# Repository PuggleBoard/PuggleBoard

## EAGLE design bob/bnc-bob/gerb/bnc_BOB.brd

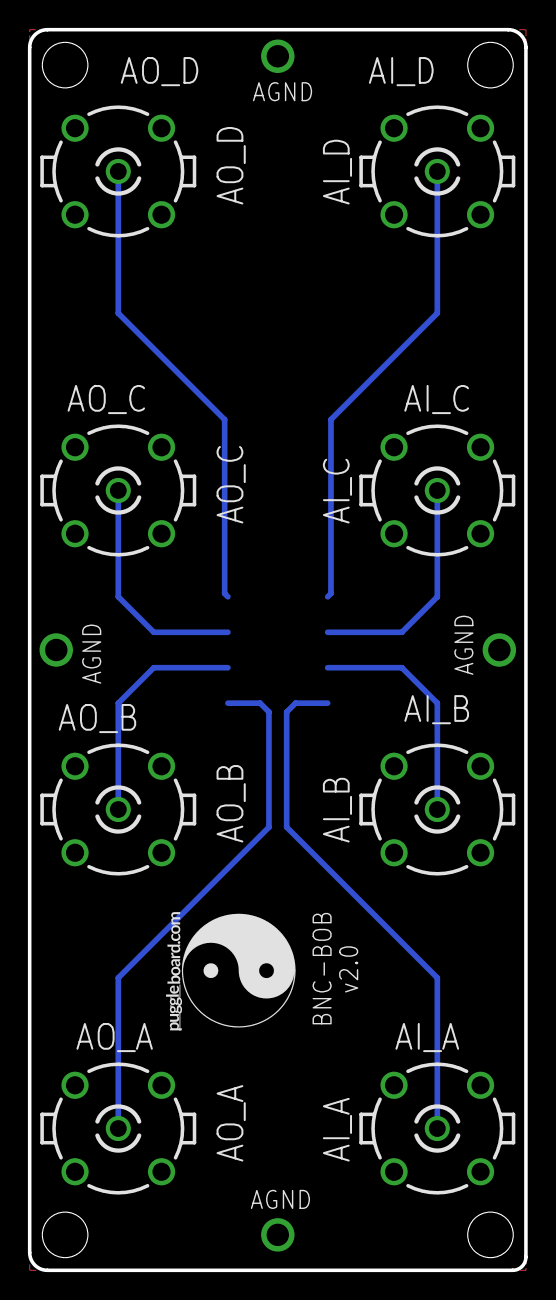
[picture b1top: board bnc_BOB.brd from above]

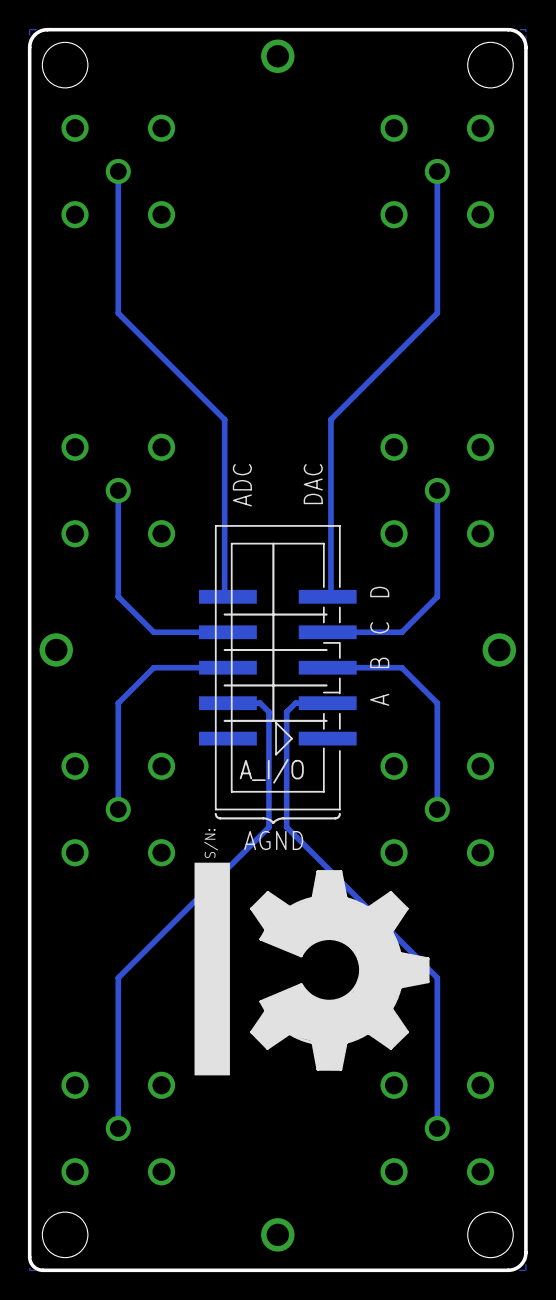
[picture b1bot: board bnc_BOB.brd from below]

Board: 2 copper layers, 35.6 x 88.9 mm, 11 parts (2 on the bottom side), 9 nets.

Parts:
AI_A: 5-1634503-1; B35N61
AI_B: 5-1634503-1; B35N61
AI_C: 5-1634503-1; B35N61
AI_D: 5-1634503-1; B35N61
AO_A: 5-1634503-1; B35N61
AO_B: 5-1634503-1; B35N61
AO_C: 5-1634503-1; B35N61
AO_D: 5-1634503-1; B35N61
A_I/O: PINHD-2X5-IDC-SMD; 2X05-IDC-SMD
U$1: PB-LOGO
U$2: OSHW_FILLX500_NOTEXT

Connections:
ADC_A: AI_A.1, A_I/O.P$4
ADC_B: AI_B.1, A_I/O.P$6
ADC_C: AI_C.1, A_I/O.P$8
ADC_D: AI_D.1, A_I/O.P$10
AGND: AI_A.2, AI_A.3, AI_A.4, AI_A.5, AI_B.2, AI_B.3, AI_B.4, AI_B.5, AI_C.2, AI_C.3, AI_C.4, AI_C.5, AI_D.2, AI_D.3, AI_D.4, AI_D.5, AO_A.2, AO_A.3, AO_A.4, AO_A.5, AO_B.2, AO_B.3, AO_B.4, AO_B.5, AO_C.2, AO_C.3, AO_C.4, AO_C.5, AO_D.2, AO_D.3, AO_D.4, AO_D.5, A_I/O.P$1, A_I/O.P$2
DAC_A: AO_A.1, A_I/O.P$3
DAC_B: AO_B.1, A_I/O.P$5
DAC_C: AO_C.1, A_I/O.P$7
DAC_D: AO_D.1, A_I/O.P$9

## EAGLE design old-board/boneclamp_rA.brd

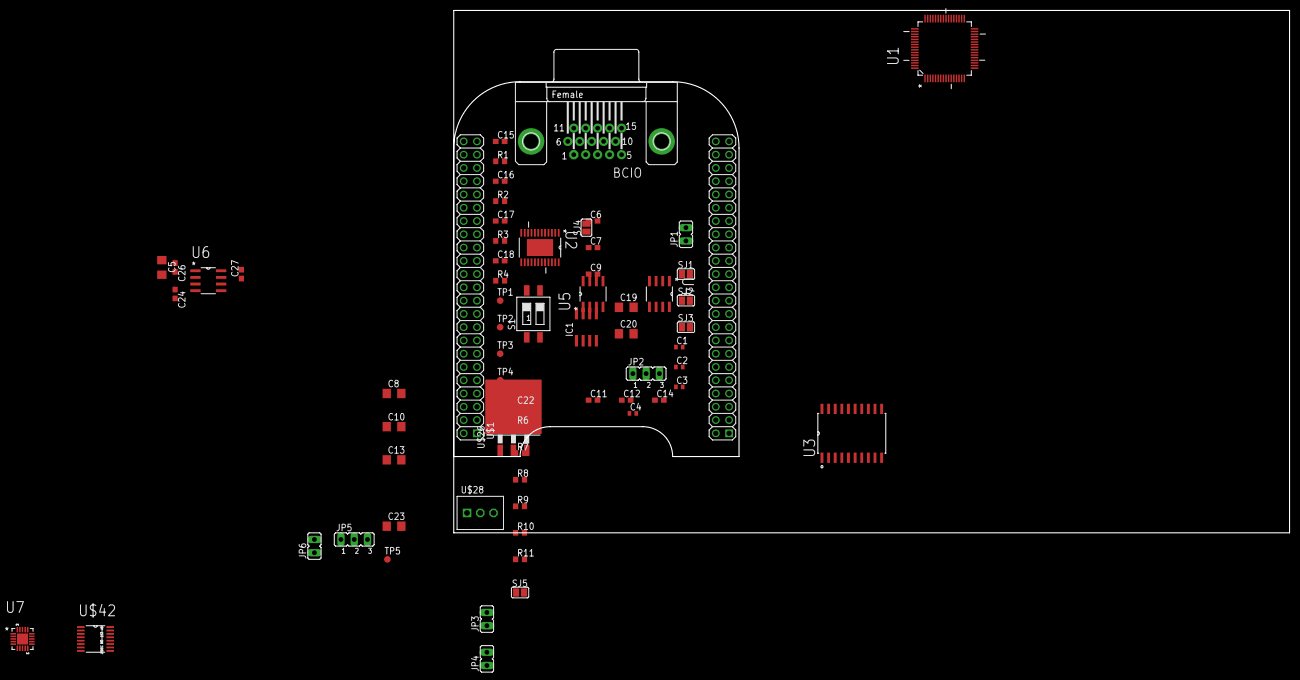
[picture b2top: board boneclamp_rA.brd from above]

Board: 4 copper layers, 160.0 x 100.0 mm, 65 parts (0 on the bottom side), 43 nets, no tracks yet.

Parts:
BCIO: F15-SHEILD; HDF15H
C1, C2, C3, C4: 1 uF; C0402
C5, C8, C10, C13, C19, C20, C23: 10uF; C1206
C6, C7, C9, C11, C12, C14, C22, C24, C26, C27: 0.1uF; C0603
C15, C16, C17, C18: C0603
IC1: 24C; SO-08
JP1, JP3, JP4, JP6: JP1
JP2, JP5: JP2
R1, R2, R3, R4: R0603
R6, R10: 5.6k; R0603
R7, R8, R9: 4.75k; R0603
R11: 10k; R0603
S1: SWS002; SMS-002
SJ1, SJ2, SJ3, SJ4, SJ5: SJ
TP1, TP2, TP3, TP4, TP5: TPB1,27; B1,27
U1: AD7656YSTZ; QFP50P1200X1200X160-64N
U2: AD5754RBREZ; SOP65P640X120-25N
U3: SN74ABT541BDW; SOIC127P1030X265-20N
U4, U5: ADP3303ARZ-5; SOIC127P600X175-8N
U6: ADR431BRZ; SOIC127P600X175-8N
U7: AD7682BCPZ; QFN50P400X400X100-21N
U$1: BEAGLEBONE_OUTLINE; BEAGLEBONE_SHIELD
U$26: LM1085; TO263-3
U$28: SCREW3
U$42: AD5686RARUZ; MO-153-AB

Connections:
+12V: C19.1, U$26.3
AGND: BCIO.1, C1.2, C2.2, C3.2, C4.2, C5.2, C6.2, C9.2, C10.2, C16.2, C17.2, C18.2, C23.2, C24.2, C26.2, JP1.2, R2.1, R3.1, R4.1, SJ4.1, U1.32, U1.37, U1.38, U1.43, U1.44, U1.49, U1.52, U1.53, U1.57, U1.59, U4.4, U5.4, U6.4, U$1.1, U$1.2, U$1.47, U$1.48, U$1.89, U$1.90, U$1.91
AVCC: C7.1, C9.1, C10.1, U4.1, U4.2
BB_5V: C5.1, C6.1, C8.1, C11.1, U4.5, U4.7, U4.8, U5.5, U5.7, U5.8, U$1.53, U$1.54
CONVST: U1.21, U1.22, U1.23
DAC_A: BCIO.8, C18.1, R4.2, TP1.TP, U2.3
DAC_B: BCIO.9, C17.1, R3.2, TP2.TP, U2.4
DAC_C: BCIO.10, C16.1, R2.2, TP3.TP, U2.23
DAC_D: BCIO.11, C15.1, R1.2, TP4.TP, U2.22
DGND: C8.2, C11.2, C13.2, C14.2, C19.2, C20.2, C22.2, IC1.4, JP2.3, S1.3, S1.4, SJ4.2, U1.8, U1.25, U$1.92, U$26.1
DVCC: C12.1, C13.1, C14.1, U1.26, U2.14, U5.1, U5.2
I2C2_SCL: IC1.6, R10.1, U$1.65
I2C2_SDA: IC1.5, R6.1, U$1.66
unnamed: BCIO.2, U1.33
unnamed: BCIO.3, U1.36
unnamed: BCIO.4, U1.39
unnamed: BCIO.5, U1.42
unnamed: BCIO.6, U1.45
unnamed: BCIO.7, U1.48
unnamed: SJ1.1, U2.16
unnamed: SJ2.2, SJ3.2, U2.9
unnamed: C2.1, U1.56
unnamed: C1.1, U1.58
unnamed: JP2.2, U1.27
unnamed: C4.1, U1.34, U1.35, U1.40, U1.41, U1.46, U1.47, U1.50, U1.60
unnamed: IC1.1, R7.1, R8.1, S1.1
unnamed: C12.2, U5.3
unnamed: C7.2, U4.3
unnamed: C15.2, R1.1
unnamed: IC1.2, S1.2
unnamed: IC1.3, R9.1
unnamed: JP3.1, U1.51
unnamed: IC1.7, SJ5.1
unnamed: R11.1, SJ5.2
unnamed: JP4.1, U2.17
unnamed: C26.1, U6.1
SGND: BCIO.P$1, BCIO.P$2, JP1.1
VDD: C23.1, C24.1, U1.31, U2.24, U6.2, U7.20, U$42.5
VDD_BB: C20.1, U$1.51, U$1.52, U$26.2, U$26.TAB
VDRIVE: C22.1, IC1.8, JP2.1, R6.2, R7.2, R8.2, R9.2, R10.2, R11.2, U$1.49, U$1.50
VREF_2.5V: JP3.2, JP4.2, JP5.2
VREF_OUT: C27.1, JP5.3, JP6.2, TP5.TP, U6.6
VSS: U1.30, U2.1

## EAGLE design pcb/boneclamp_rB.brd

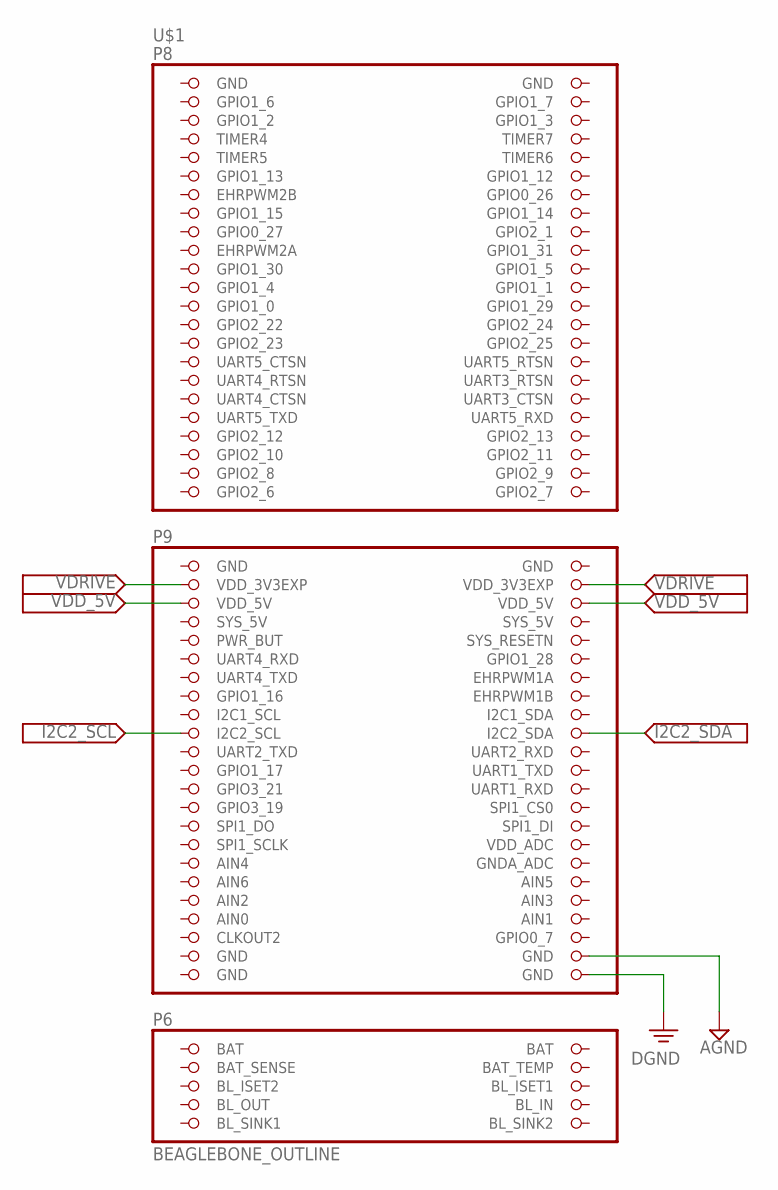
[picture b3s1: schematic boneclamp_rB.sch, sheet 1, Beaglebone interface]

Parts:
U$1: BEAGLEBONE_OUTLINE; BEAGLEBONE_SHIELD

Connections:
AGND: U$1.90 (GND); also elsewhere on the board
AIN0: U$1.85 (AIN0)
BAT_SENSE: U$1.95 (BAT_SENSE)
BL_IN: U$1.97 (BL_IN)
BL_OUT: U$1.100 (BL_OUT)
BL_SINK1: U$1.101 (BL_SINK1)
BL_SINK2: U$1.102 (BL_SINK2)
DGND: U$1.92 (GND); also elsewhere on the board
GND: U$1.1 (GND), U$1.2 (GND), U$1.47 (GND), U$1.48 (GND), U$1.89 (GND), U$1.91 (GND); also elsewhere on the board
I2C2_SCL: U$1.65 (I2C2_SCL); also elsewhere on the board
I2C2_SDA: U$1.66 (I2C2_SDA); also elsewhere on the board
SYS_5V: U$1.53 (SYS_5V)
VDD_5V: U$1.51 (VDD_5V), U$1.52 (VDD_5V); also elsewhere on the board
VDRIVE: U$1.49 (VDD_3V3EXP), U$1.50 (VDD_3V3EXP); also elsewhere on the board

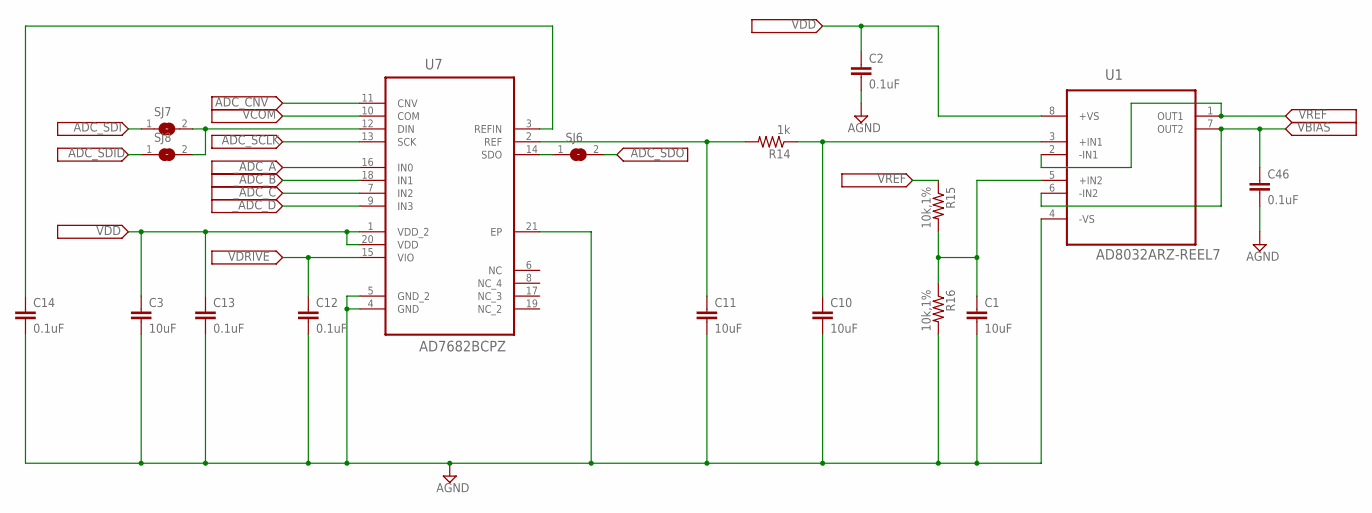
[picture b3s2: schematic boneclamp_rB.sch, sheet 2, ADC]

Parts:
C1, C3, C10, C11: 10uF; C0805
C2, C12, C13, C14, C46: 0.1uF; C0805
R14: 1k; R0805
R15, R16: 10k,1%; R0805
SJ6, SJ7, SJ8: SJ
U1: AD8032ARZ-REEL7; SOIC127P600X175-8N
U7: AD7682BCPZ; QFN50P400X400X100-21N

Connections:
ADC_CNV: U7.11 (CNV)
ADC_SCLK: U7.13 (SCK)
ADC_SDI: SJ7.1
ADC_SDID: SJ8.1
ADC_SDO: SJ6.2
AGND: C1.2, C2.2, C3.2, C10.2, C11.2, C12.2, C13.2, C14.2, C46.2, R16.2, U1.4 (-VS), U7.4 (GND), U7.5 (GND_2), U7.21 (EP); also elsewhere on the board
unnamed: C1.1, R15.2, R16.1, U1.5 (+IN2)
unnamed: SJ7.2, SJ8.2, U7.12 (DIN)
unnamed: C11.1, R14.2, U7.2 (REF)
unnamed: C10.1, R14.1, U1.3 (+IN1)
unnamed: C14.1, U7.3 (REFIN)
VBIAS: C46.1, U1.6 (-IN2), U1.7 (OUT2); also elsewhere on the board
VCOM: U7.10 (COM)
VDD: C2.1, C3.1, C13.1, U1.8 (+VS), U7.1 (VDD_2), U7.20 (VDD); also elsewhere on the board
VDRIVE: C12.1, U7.15 (VIO); also elsewhere on the board
VREF: R15.1, U1.1 (OUT1), U1.2 (-IN1); also elsewhere on the board
_ADC_A: U7.16 (IN0); also elsewhere on the board
_ADC_B: U7.18 (IN1); also elsewhere on the board
_ADC_C: U7.7 (IN2); also elsewhere on the board
_ADC_D: U7.9 (IN3); also elsewhere on the board

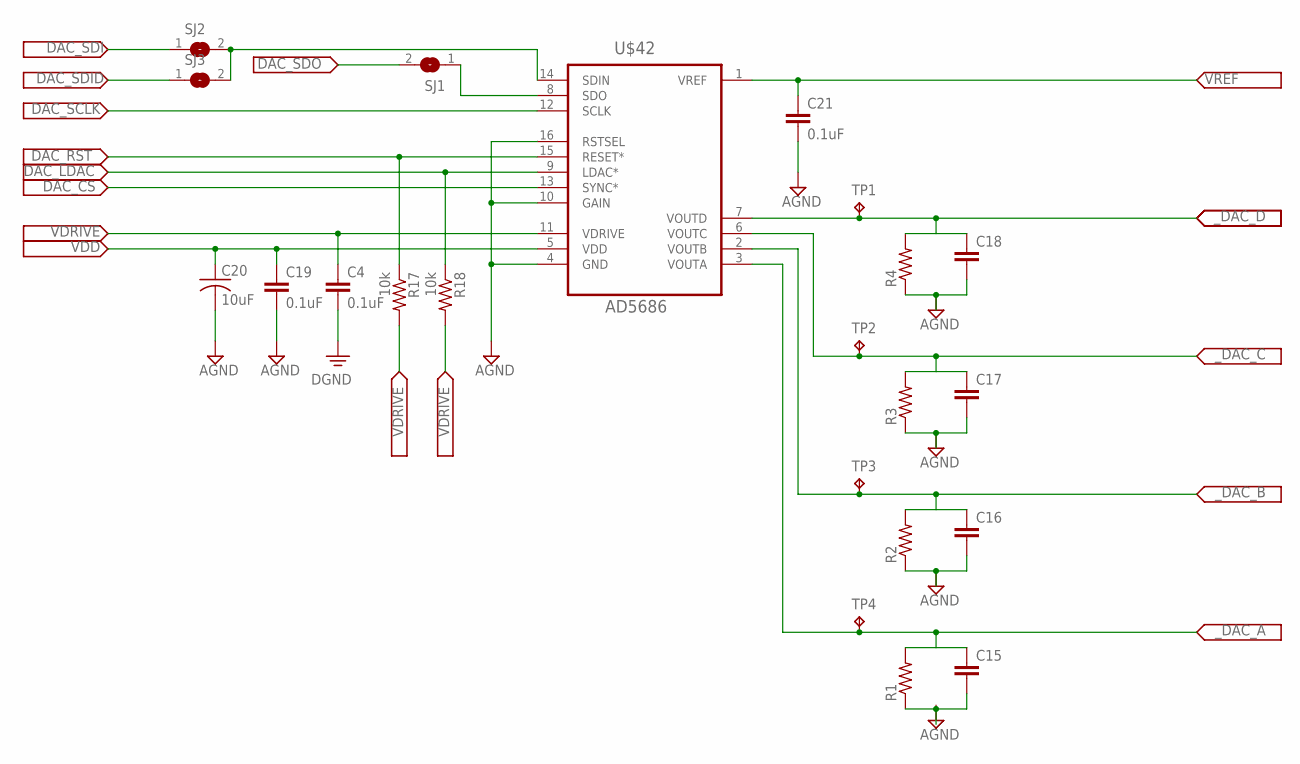
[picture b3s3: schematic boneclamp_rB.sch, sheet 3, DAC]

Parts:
C4, C19, C21: 0.1uF; C0805
C15, C16, C17, C18: C-EUC0805; C0805
C20: 10uF; C0805
R1, R2, R3, R4: R-US_R0805; R0805
R17, R18: 10k; R0805
SJ1, SJ2, SJ3: SJ
TP1, TP2, TP3, TP4: TPB1,27; B1,27
U$42: AD5686; MO-153-AB

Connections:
AGND: C16.2, C17.2, C18.2, C19.2, C20.2, C21.2, R2.1, R3.1, R4.1, U$42.4 (GND), U$42.10 (GAIN), U$42.16 (RSTSEL); also elsewhere on the board
DAC_CS: U$42.13 (SYNC*)
DAC_LDAC: R18.1, U$42.9 (LDAC*)
DAC_RST: R17.1, U$42.15 (RESET*)
DAC_SCLK: U$42.12 (SCLK)
DAC_SDI: SJ2.1
DAC_SDID: SJ3.1
DAC_SDO: SJ1.2
unnamed: SJ1.1, U$42.8 (SDO)
unnamed: SJ2.2, SJ3.2, U$42.14 (SDIN)
unnamed: C15.2, R1.1
PE: C4.2
VDD: C19.1, C20.1, U$42.5 (VDD); also elsewhere on the board
VDRIVE: C4.1, R17.2, R18.2, U$42.11 (VDRIVE); also elsewhere on the board
VREF: C21.1, U$42.1 (VREF); also elsewhere on the board
_DAC_A: C15.1, R1.2, TP4.TP, U$42.3 (VOUTA); also elsewhere on the board
_DAC_B: C16.1, R2.2, TP3.TP, U$42.2 (VOUTB); also elsewhere on the board
_DAC_C: C17.1, R3.2, TP2.TP, U$42.6 (VOUTC); also elsewhere on the board
_DAC_D: C18.1, R4.2, TP1.TP, U$42.7 (VOUTD); also elsewhere on the board

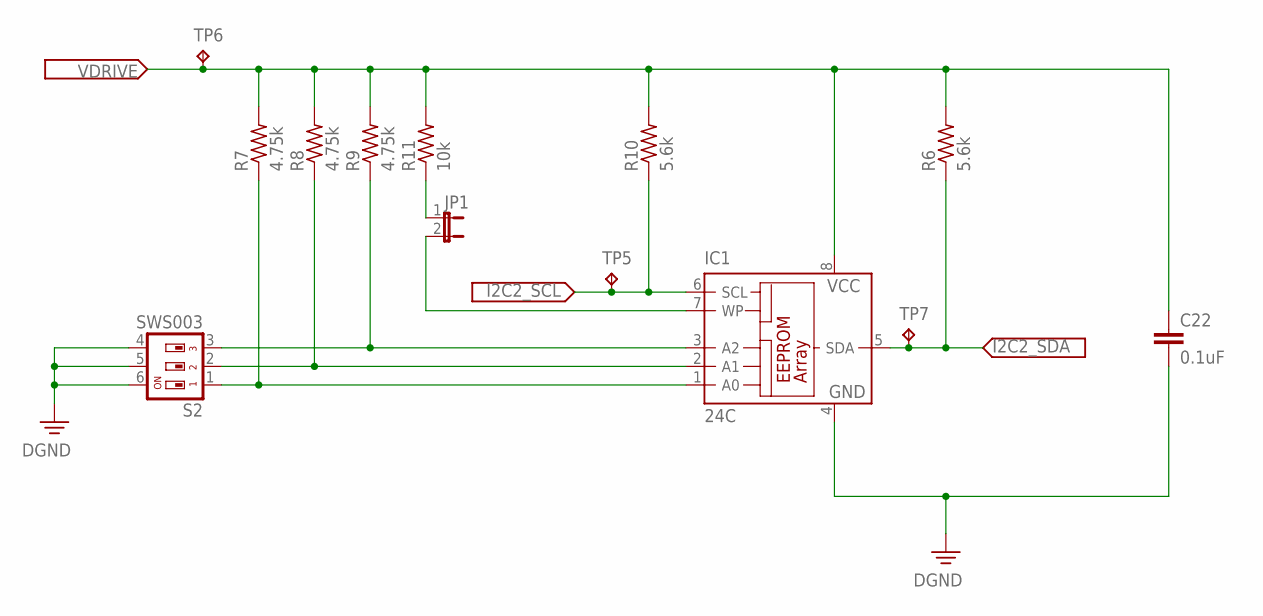
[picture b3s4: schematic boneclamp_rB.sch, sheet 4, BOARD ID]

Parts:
C22: 0.1uF; C0603
IC1: 24C; SO-08
JP1: JP1E; JP1
R6, R10: 5.6k; R0603
R7, R8, R9: 4.75k; R0603
R11: 10k; R0603
S2: SWS003; SMS-003
TP5, TP6, TP7: TPB1,27; B1,27

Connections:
DGND: C22.2, IC1.4 (GND), S2.4, S2.5, S2.6; also elsewhere on the board
I2C2_SCL: IC1.6 (SCL), R10.1, TP5.TP; also elsewhere on the board
I2C2_SDA: IC1.5 (SDA), R6.1, TP7.TP; also elsewhere on the board
unnamed: IC1.1 (A0), R7.1, S2.1
unnamed: IC1.2 (A1), R8.1, S2.2
unnamed: IC1.3 (A2), R9.1, S2.3
unnamed: IC1.7 (WP), JP1.2
unnamed: JP1.1, R11.1
VDRIVE: C22.1, IC1.8 (VCC), R6.2, R7.2, R8.2, R9.2, R10.2, R11.2, TP6.TP; also elsewhere on the board

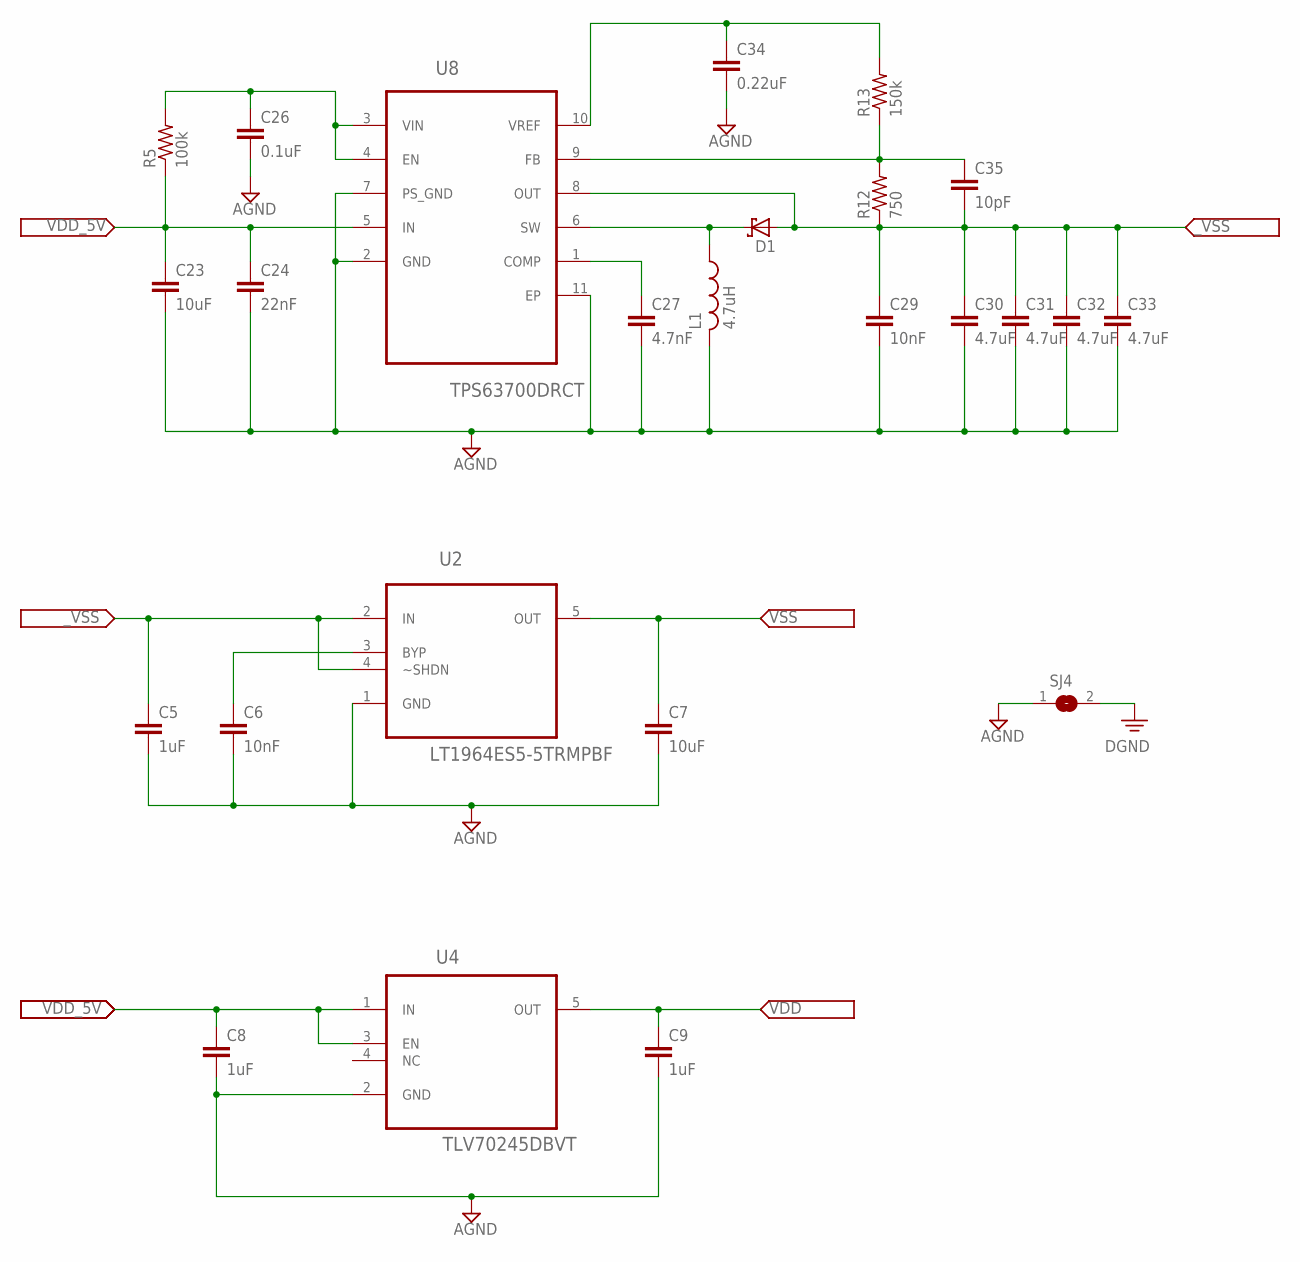
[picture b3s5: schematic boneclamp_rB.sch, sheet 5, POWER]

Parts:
C5, C8, C9: 1uF; C0603
C6, C29: 10nF; C0603
C7, C23: 10uF; C0603
C24: 22nF; C0603
C26: 0.1uF; C0603
C27: 4.7nF; C0603
C30, C31, C32, C33: 4.7uF; C0603
C34: 0.22uF; C0603
C35: 10pF; C0603
D1: SCHOTTKY-DIODE-2; DO-219AB
L1: 4.7uH; L4012M
R5: 100k; R0603
R12: 750; R0603
R13: 150k; R0603
SJ4: SJ
U2: LT1964ES5-5TRMPBF; SOT95P280X100-5N
U4: TLV70245DBVT; SOT95P280X110-5N
U8: TPS63700DRCT; SON50P300X300X100-11N

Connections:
AGND: C5.2, C6.2, C7.2, C8.2, C9.2, C23.2, C24.2, C26.2, C27.2, C29.2, C30.2, C31.2, C32.2, C33.2, C34.2, L1.2, SJ4.1, U2.1 (GND), U4.2 (GND), U8.2 (GND), U8.7 (PS_GND), U8.11 (EP); also elsewhere on the board
DGND: SJ4.2; also elsewhere on the board
unnamed: C6.1, U2.3 (BYP)
unnamed: C26.1, R5.2, U8.3 (VIN), U8.4 (EN)
unnamed: C27.1, U8.1 (COMP)
unnamed: D1.P$1 (A), L1.1, U8.6 (SW)
unnamed: C35.1, R12.2, R13.1, U8.9 (FB)
unnamed: C34.1, R13.2, U8.10 (VREF)
VDD: C9.1, U4.5 (OUT); also elsewhere on the board
VDD_5V: C8.1, C23.1, C24.1, R5.1, U4.1 (IN), U4.3 (EN), U8.5 (IN); also elsewhere on the board
VSS: C7.1, U2.5 (OUT); also elsewhere on the board
_VSS: C5.1, C29.1, C30.1, C31.1, C32.1, C33.1, C35.2, D1.P$2 (C), R12.1, U2.2 (IN), U2.4 (~SHDN), U8.8 (OUT)

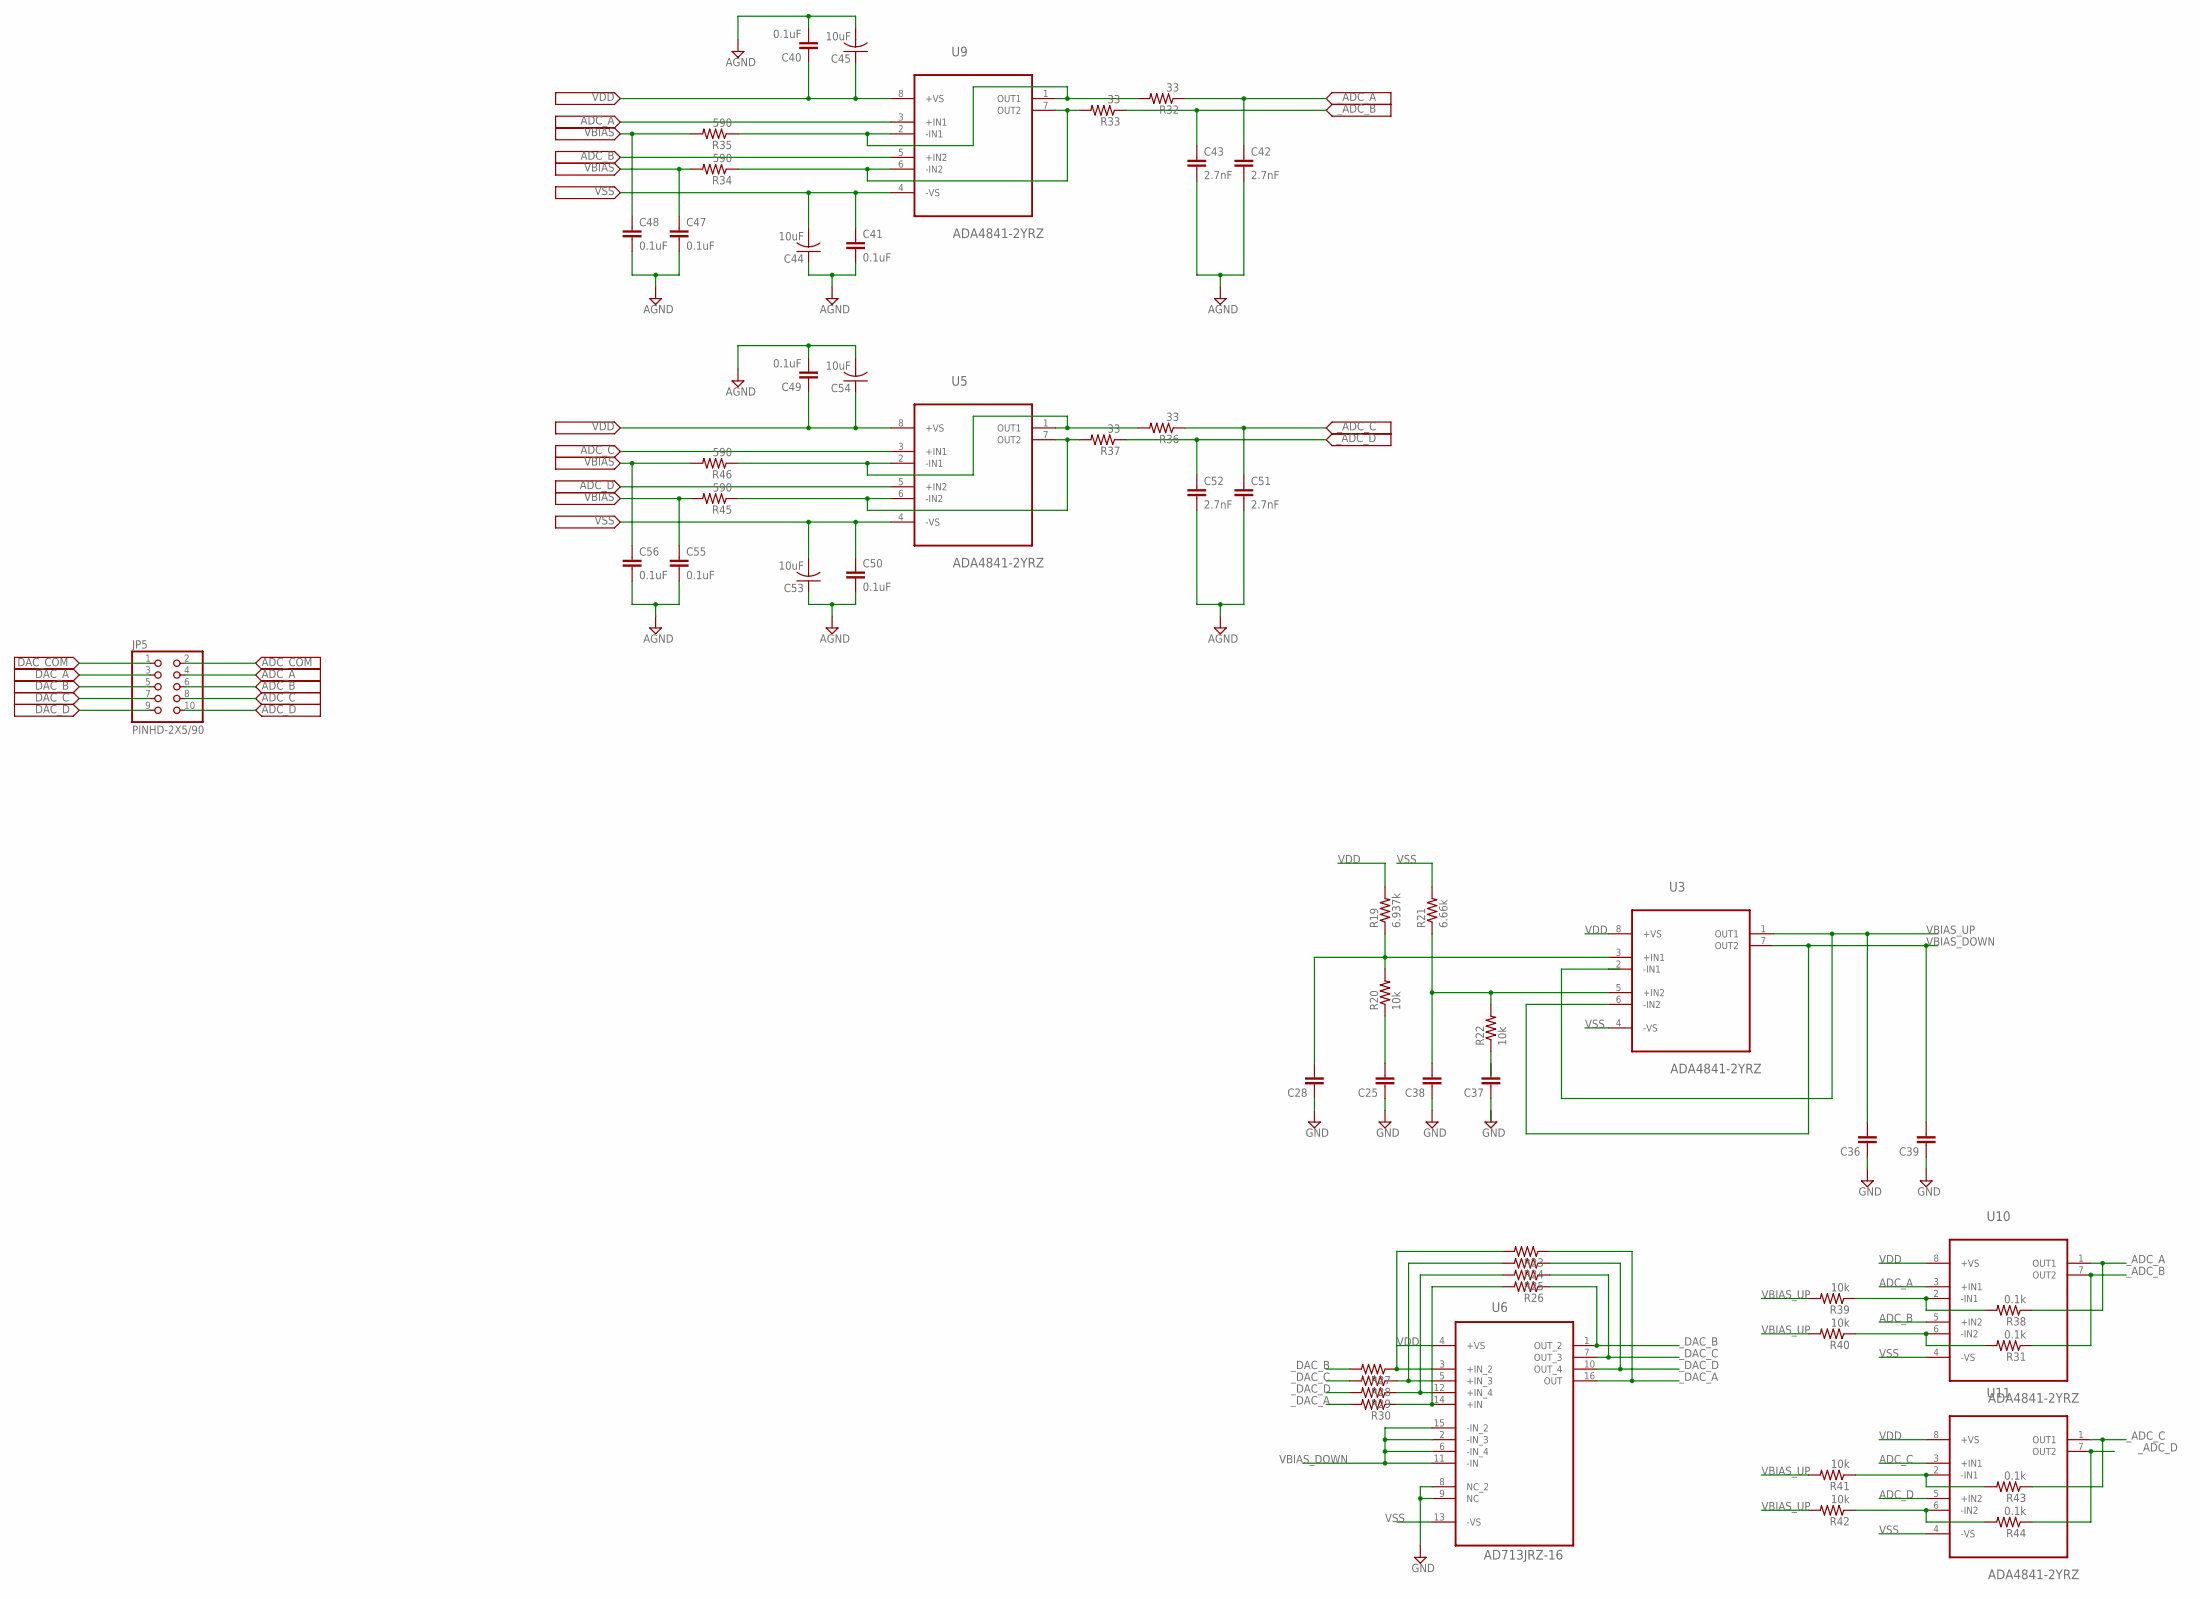
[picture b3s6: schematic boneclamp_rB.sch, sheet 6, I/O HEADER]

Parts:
C25, C28, C36, C37, C38, C39: C-EU025-025X050; C025-025X050
C40, C41, C47, C48, C49, C50, C55, C56: 0.1uF; C0805
C42, C43, C51, C52: 2.7nF; C0805
C44, C45, C53, C54: 10uF; C0805
JP5: PINHD-2X5/90; 2X05/90
R19: 6.937k; 0204V
R20, R22: 10k; 0204V
R21: 6.66k; 0204V
R23, R24, R25, R26, R27, R28, R29, R30: R-US_0204/2V; 0204V
R31, R38, R43, R44: 0.1k; R0805
R32, R33, R36, R37: 33; R0603
R34, R35, R45, R46: 590; R0603
R39, R40, R41, R42: 10k; R0805
U3, U5, U9, U10, U11: ADA4841-2YRZ; SOIC127P600X175-8N
U6: AD713JRZ-16; SOIC127P1032X265-16N

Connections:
ADC_A: JP5.4, U9.3 (+IN1), U10.3 (+IN1)
ADC_B: JP5.6, U9.5 (+IN2), U10.5 (+IN2)
ADC_C: JP5.8, U5.3 (+IN1), U11.3 (+IN1)
ADC_COM: JP5.2
ADC_D: JP5.10, U5.5 (+IN2), U11.5 (+IN2)
AGND: C40.2, C41.2, C42.2, C43.2, C44.1, C45.2, C47.2, C48.2, C49.2, C50.2, C51.2, C52.2, C53.1, C54.2, C55.2, C56.2; also elsewhere on the board
DAC_A: JP5.3
DAC_B: JP5.5
DAC_C: JP5.7
DAC_COM: JP5.1
DAC_D: JP5.9
GND: C25.1, C28.1, C36.1, C38.1, C39.1, U6.8 (NC_2), U6.9 (NC); also elsewhere on the board
unnamed: R37.2, R45.1, U5.6 (-IN2), U5.7 (OUT2)
unnamed: R33.2, R34.1, U9.6 (-IN2), U9.7 (OUT2)
unnamed: R26.2, R30.1, U6.14 (+IN)
unnamed: R36.2, R46.1, U5.1 (OUT1), U5.2 (-IN1)
unnamed: R32.2, R35.1, U9.1 (OUT1), U9.2 (-IN1)
unnamed: R25.2, R29.1, U6.12 (+IN_4)
unnamed: C38.2, R21.1, R22.2, U3.5 (+IN2)
unnamed: C28.2, R19.1, R20.2, U3.3 (+IN1)
unnamed: R24.2, R28.1, U6.5 (+IN_3)
unnamed: R23.2, R27.1, U6.3 (+IN_2)
unnamed: C25.2, R20.1
VBIAS: C47.1, C48.1, C55.1, C56.1, R34.2, R35.2, R45.2, R46.2; also elsewhere on the board
VBIAS_DOWN: C39.2, U3.6 (-IN2), U3.7 (OUT2), U6.2 (-IN_3), U6.6 (-IN_4), U6.11 (-IN), U6.15 (-IN_2)
VBIAS_UP: C36.2, R31.2, R38.2, R39.1, R39.2, R40.1, R40.2, R41.1, R41.2, R42.1, R42.2, R43.2, R44.2, U3.1 (OUT1), U3.2 (-IN1), U10.2 (-IN1), U10.6 (-IN2), U11.2 (-IN1), U11.6 (-IN2)
VDD: C40.1, C45.1, C49.1, C54.1, R19.2, U3.8 (+VS), U5.8 (+VS), U6.4 (+VS), U9.8 (+VS), U10.8 (+VS), U11.8 (+VS); also elsewhere on the board
VSS: C41.1, C44.2, C50.1, C53.2, R21.2, U3.4 (-VS), U5.4 (-VS), U6.13 (-VS), U9.4 (-VS), U10.4 (-VS), U11.4 (-VS); also elsewhere on the board
_ADC_A: C42.1, R32.1, R38.1, U10.1 (OUT1); also elsewhere on the board
_ADC_B: C43.1, R31.1, R33.1, U10.7 (OUT2); also elsewhere on the board
_ADC_C: C51.1, R36.1, R43.1, U11.1 (OUT1); also elsewhere on the board
_ADC_D: C52.1, R37.1, R44.1, U11.7 (OUT2); also elsewhere on the board
_DAC_A: R23.1, R30.2, U6.16 (OUT); also elsewhere on the board
_DAC_B: R26.1, R27.2, U6.1 (OUT_2); also elsewhere on the board
_DAC_C: R25.1, R28.2, U6.7 (OUT_3); also elsewhere on the board
_DAC_D: R24.1, R29.2, U6.10 (OUT_4); also elsewhere on the board

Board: 4 copper layers, 135 parts (0 on the bottom side), 58 nets, no tracks yet.

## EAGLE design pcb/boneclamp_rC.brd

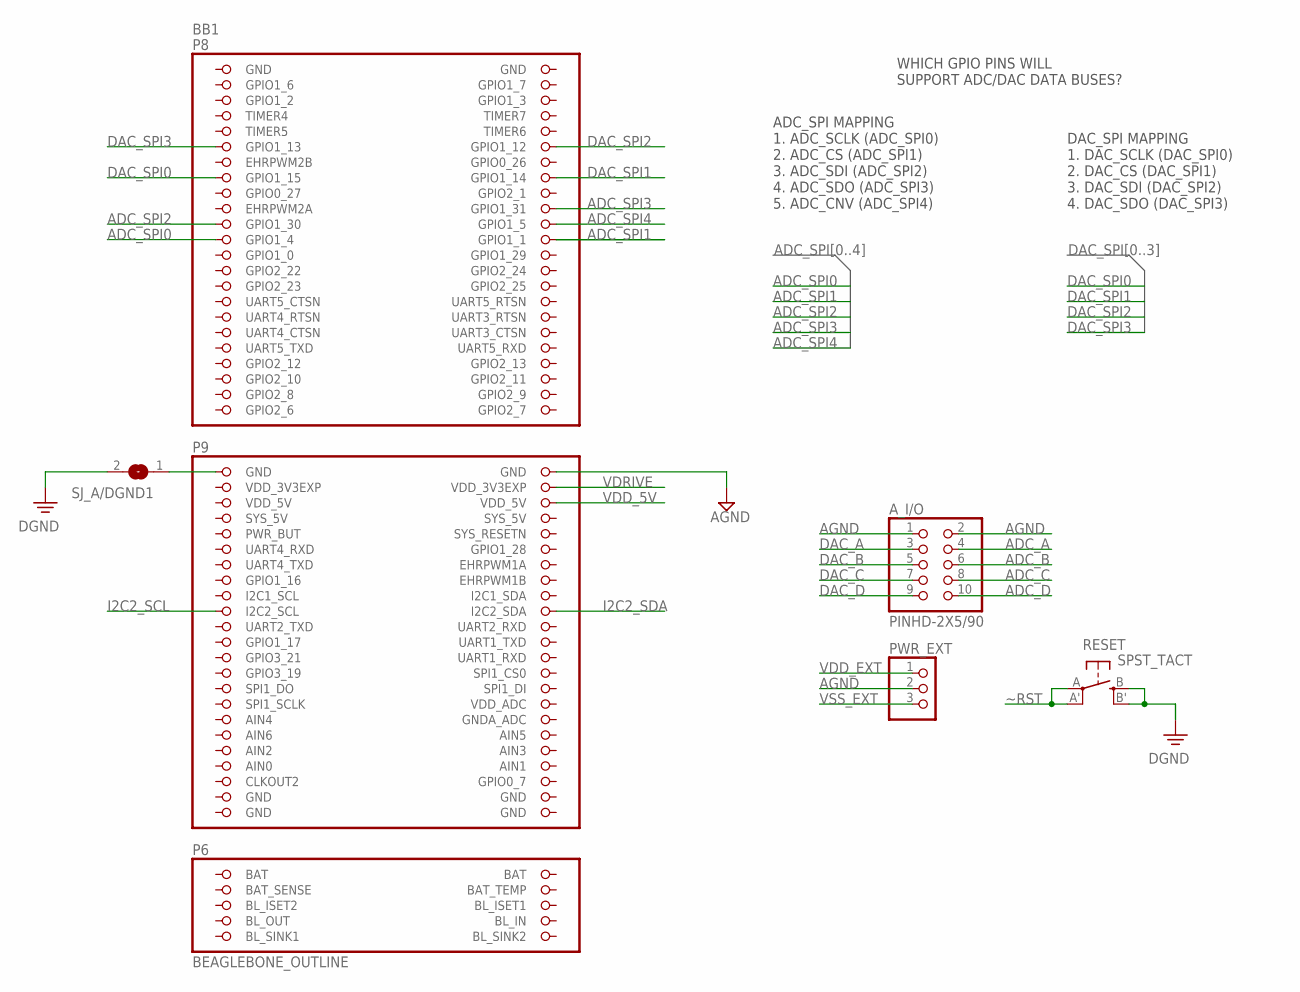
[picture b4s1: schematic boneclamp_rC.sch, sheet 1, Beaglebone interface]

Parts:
A_I/O: PINHD-2X5/90; 2X05/90
BB1: BEAGLEBONE_OUTLINE; BEAGLEBONE_SHIELD
PWR_EXT: PINHD-1X3; 1X03
RESET: SPST_TACT; EVQ-Q2-A
SJ_A/DGND1: SJ

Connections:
ADC_A: A_I/O.4; also elsewhere on the board
ADC_B: A_I/O.6; also elsewhere on the board
ADC_C: A_I/O.8; also elsewhere on the board
ADC_D: A_I/O.10; also elsewhere on the board
ADC_SPI0: BB1.23 (GPIO1_4); also elsewhere on the board
ADC_SPI1: BB1.24 (GPIO1_1); also elsewhere on the board
ADC_SPI2: BB1.21 (GPIO1_30); also elsewhere on the board
ADC_SPI3: BB1.20 (GPIO1_31); also elsewhere on the board
ADC_SPI4: BB1.22 (GPIO1_5); also elsewhere on the board
AGND: A_I/O.1, A_I/O.2, BB1.48 (GND), PWR_EXT.2; also elsewhere on the board
AIN0: BB1.85 (AIN0)
BAT_SENSE: BB1.95 (BAT_SENSE)
BL_IN: BB1.97 (BL_IN)
BL_OUT: BB1.100 (BL_OUT)
BL_SINK1: BB1.101 (BL_SINK1)
BL_SINK2: BB1.102 (BL_SINK2)
DAC_A: A_I/O.3; also elsewhere on the board
DAC_B: A_I/O.5; also elsewhere on the board
DAC_C: A_I/O.7; also elsewhere on the board
DAC_D: A_I/O.9; also elsewhere on the board
DAC_SPI0: BB1.15 (GPIO1_15); also elsewhere on the board
DAC_SPI1: BB1.16 (GPIO1_14); also elsewhere on the board
DAC_SPI2: BB1.12 (GPIO1_12); also elsewhere on the board
DAC_SPI3: BB1.11 (GPIO1_13); also elsewhere on the board
DGND: RESET.B (S), RESET.B' (S1), SJ_A/DGND1.2; also elsewhere on the board
GND: BB1.1 (GND), BB1.2 (GND), BB1.89 (GND), BB1.90 (GND), BB1.91 (GND), BB1.92 (GND)
I2C2_SCL: BB1.65 (I2C2_SCL); also elsewhere on the board
I2C2_SDA: BB1.66 (I2C2_SDA); also elsewhere on the board
unnamed: BB1.47 (GND), SJ_A/DGND1.1
SYS_5V: BB1.53 (SYS_5V)
VDD_3V3EXP: BB1.49 (VDD_3V3EXP)
VDD_5V: BB1.51 (VDD_5V), BB1.52 (VDD_5V); also elsewhere on the board
VDD_EXT: PWR_EXT.1; also elsewhere on the board
VDRIVE: BB1.50 (VDD_3V3EXP); also elsewhere on the board
VSS_EXT: PWR_EXT.3; also elsewhere on the board
~RST: RESET.A, RESET.A' (P1); also elsewhere on the board

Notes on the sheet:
ADC_SPI MAPPING 1. ADC_SCLK (ADC_SPI0) 2. ADC_CS (ADC_SPI1) 3. ADC_SDI (ADC_SPI2) 4. ADC_SDO (ADC_SPI3) 5. ADC_CNV (ADC_SPI4)
DAC_SPI MAPPING 1. DAC_SCLK (DAC_SPI0) 2. DAC_CS (DAC_SPI1) 3. DAC_SDI (DAC_SPI2) 4. DAC_SDO (DAC_SPI3)
WHICH GPIO PINS WILL SUPPORT ADC/DAC DATA BUSES?
